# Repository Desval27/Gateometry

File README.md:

# Gateometry

Eight-channel Euclidean rhythm generator for a **classic Arduino Nano, ATmega328P,
16 MHz / 5 V**, using a **128×64 SSD1306 I2C OLED** and Adafruit GFX. This does not
target the Nano Every, Nano ESP32, or a SH1106 display.

## Resources

!Untested!

- [PCB](hardware/README.md)
- [Panel](panel/README.md)

## Build and upload

```sh
pio run
pio run -t upload
```

The existing `nanoatmega328` environment is retained. It uses the old Nano
bootloader setting. For a newer bootloader, change the `board` setting to
`nanoatmega328new`; the environment name can stay unchanged. If necessary set
`upload_port` in `platformio.ini`. PlatformIO installs the Adafruit dependencies.

The sketch starts **stopped**, using the internal clock at **120 BPM**, with
**4 steps per beat** (sixteenth notes). All channels start with **N=16, K=4,
rotation=0, duty=50%**. Settings are RAM-only and return to defaults at power-up.

## Controls and display

- **Run/Stop button:** stop immediately clears all channel gates after button
  debounce. Starting resets every channel and plays slot zero on the next clock
  rising edge. The clock itself keeps running and remains available at Clock Out.
- **Overview:** rotate the encoder to select the header or one of eight channels;
  click to open the selected editor. The header opens global clock settings.
- **Inside either editor:** turn to change the highlighted parameter; click to
  select the next parameter. Hold for 600 ms to return to the overview.
- **Global editor:** choose Internal/External, BPM (20–300), and steps per beat
  (1, 2, 4, or 8). For source selection, clockwise selects External and
  counterclockwise selects Internal. BPM and steps/beat apply to the internal
  clock and the initial external gate-length estimate.
- **Channel editor:** N=1–32, K=0–N, signed rotation=−(N−1)…+(N−1), duty=1–99%.
  Reducing N clamps K and rotation to valid values. Changing a channel parameter
  clears its gate and restarts that channel at slot zero on the next clock;
  the other channels retain their position.
- **Mute toggles:** closed to ground = muted; open = enabled. Muting clears the
  gate after switch debounce; the channel continues counting slots. Unmuting
  waits for the next eligible hit, so it does not create a partial pulse.

Each overview necklace shows every slot, filled hits, and a radial playhead.
Slot zero is at twelve o'clock; time and positive rotation run clockwise.
A diagonal slash marks a muted channel; a small square indicates its gate is
currently high. The selected channel gets a border. The detail page enlarges
its necklace. At 32 slots the small overview is necessarily dense; use the
larger editor to inspect individual slots. The OLED refreshes at about 15 fps,
so very short pulses may not appear in every frame; physical LEDs follow gates.

## Clock and gate behavior

One clock rising edge advances **one slot on every channel**. Each channel wraps
at its own N. For example, N=5 and N=7 realign after 35 clock edges. Euclidean
onsets are evenly distributed with the first unrotated hit at slot zero:
N=8/K=3 gives `10010010`. A positive rotation of one gives `01001001`.

Internal clock interval is `60000 / (BPM × stepsPerBeat)` milliseconds, with a
fractional accumulator to avoid cumulative integer-rounding drift. Clock Out
and the clock LED use approximately 50% duty, and operate even while stopped.
The selected source is explicit; inserting a cable does not automatically
change sources. Changing source clears gates and resets channel positions.

External clock input uses D4's pin-change interrupt. Clock Out and its LED
follow **both edges** of the conditioned input, including while stopped. This
preserves incoming pulse width, with interrupt latency; it is a logic-level
copy, not an analog voltage copy. There is no clock multiplication or division
in external mode: feed a sixteenth-note clock if that is the desired slot rate.

External rising edges closer than 20 ms to the last accepted edge are ignored
by the sequencer (maximum accepted step rate 50 Hz), although Clock Out still
copies them. Use clean, debounced clock edges; this interval guard is not a
replacement for input conditioning. Period measurement supports 20–10,000 ms.
The first pulse, and the first after a gap longer than 10 seconds, uses the
internal BPM/steps setting to estimate its gate length. Following pulses use
the latest measured rising-to-rising interval. The header displays that interval
in milliseconds; `WAIT` appears after the longer of one second or three estimated
periods without a new accepted edge. It does not switch to the internal clock.
If the input stays high, Clock Out stays high as well.

Channel duty is a percentage of **one slot interval**, not the time between
filled slots. Width is quantized to milliseconds, with a minimum of one timer
tick and a maximum one tick shorter than the estimated interval. This leaves a
low gap between adjacent hits. When an external clock suddenly accelerates
before a previous gate has finished, that gate is lowered and retriggered on
the next 1 kHz timer tick. External widths depend on the previous interval,
so abrupt tempo changes cannot have a perfectly predicted duty cycle. If the
external clock disappears, active channel gates still expire normally.

## Nano pin allocation

The pin assignments are fixed in `src/main.cpp`. D2/D3, D4, D5/D6, and D10 use
AVR port/interrupt registers as well as Arduino pin constants; changing those
constants alone is insufficient to move these signals.

| Nano pin | Connection |
| --- | --- |
| D2 / INT0 | Encoder A, contact to ground, internal pull-up |
| D3 / INT1 | Encoder B, contact to ground, internal pull-up |
| D4 / PCINT20 | Conditioned external clock, active high, 0–5 V |
| D5 | Clock Out logic, through output buffer to jack |
| D6 | Clock LED anode through 2.2–4.7 kΩ; cathode to ground |
| D7 | 74HC165 SH/LD (active-low parallel load) |
| D8 | 74HC165 CLK |
| D9 | 74HC165 QH (non-inverted serial output) |
| D10 | 74HC595 RCLK (output latch) |
| D11 / MOSI | 74HC595 SER (serial data) |
| D13 / SCK | 74HC595 SRCLK (shift clock) |
| A0 | Encoder push switch to ground, internal pull-up |
| A1 | 74HC595 OE, with external 10 kΩ pull-up to +5 V |
| A2 | Run/Stop push switch to ground, internal pull-up |
| A4 / SDA | OLED SDA |
| A5 / SCL | OLED SCL |
| D0/D1, D12, A3 | Spare |
| A6/A7 | Unused; analog input only on this Nano |

The encoder common terminal goes to ground. No encoder or button pin is shared
with a jack. Quadrature decoding runs on both encoder interrupts. Set
`EncoderDirection` to −1 if needed; set `EncoderTransitions` to 2 for an encoder
that produces two transitions per detent instead of four.

OLED address defaults to `0x3C`; change `OledAddress` to `0x3D` if necessary.
Use a module compatible with the Nano's 5 V I2C levels, or add appropriate
level translation. A bare SSD1306 panel is not a drop-in 5 V module. The sketch
assumes the module supplies its own reset circuit (no dedicated OLED reset pin).
Use suitable I2C pull-ups and short wiring for the 400 kHz bus.

## Shift registers and output stages

Use **one 74HC595** for the eight gate logic signals, and **one 74HC165** for
the eight mute switches. The 165 uses a separate clock so switch scanning cannot
interfere with interrupt-driven gate updates. Gate LEDs can follow the buffered
gate signals, so no additional LED shift register is necessary.

For the usual 16-pin packages, verify the chosen manufacturer's pinout:

| 74HC595 signal | IC pin | Wire to |
| --- | --- | --- |
| VCC / GND | 16 / 8 | +5 V / ground |
| SER / SRCLK / RCLK | 14 / 11 / 12 | Nano D11 / D13 / D10 |
| OE | 13 | Nano A1 and 10 kΩ pull-up to +5 V |
| SRCLR | 10 | +5 V |
| QA | 15 | Channel 1 buffer input |
| QB…QH | 1…7 | Channels 2…8 buffer inputs |
| QH' | 9 | Unconnected |

Add a 100 kΩ pull-down at each buffer input driven by QA…QH. OE is held high
through reset and bootloader activity; these pull-downs define a low while the
595 outputs are high impedance. The sketch latches zeros before enabling OE.

| 74HC165 signal | IC pin | Wire to |
| --- | --- | --- |
| VCC / GND | 16 / 8 | +5 V / ground |
| SH/LD / CLK / QH | 1 / 2 / 9 | Nano D7 / D8 / D9 |
| CLK INH | 15 | Ground |
| SER | 10 | Ground |
| A / B / C / D | 11 / 12 / 13 / 14 | Channel 1 / 2 / 3 / 4 mute switch |
| E / F / G / H | 3 / 4 / 5 / 6 | Channel 5 / 6 / 7 / 8 mute switch |
| Inverted QH | 7 | Unconnected |

Each A…H input needs its **own 10 kΩ pull-up to +5 V** and a toggle switch to
ground. There are no internal pull-ups in the 165. Place 100 nF decoupling
capacitors at both registers and every buffer IC.

A practical prototype output arrangement is two **74AHCT541 non-inverting
octal buffers**, powered from +5 V. One serves the eight gate outputs; one
channel of the second serves Clock Out. Tie both active-low enables on each
buffer to ground, tie unused inputs to ground, and leave unused outputs open.
Add a 100 kΩ pull-down on the Clock Out buffer input as well.

```text
595 QA..QH ----+--> 74AHCT541 input
              |
             100k
              |
             GND

buffer output ---- 1k ---- gate jack tip
       |
       +---- 4.7k ---- LED anode; LED cathode to GND

Nano D5 --> buffered identically --> clock jack tip
jack sleeves ---------------------> common GND
```

This provides nominal 0/+5 V gates for modules that accept 5 V logic gates.
The series resistor limits short-circuit current and isolates cable loading;
keep per-pin and total package current within the buffer datasheet ratings.
Take the LED branch before the jack's series resistor. The clock LED already
has its own Nano D6 drive. The 595 only drives buffer inputs in this arrangement.
This is a prototype interface suggestion, not a fully protected Eurorack output
circuit: patching an output against an external voltage requires suitable
additional protection, and modules requiring higher gates need another driver.

**Do not connect a raw Eurorack clock jack directly to D4.** A practical
through-hole prototype input stage uses two gates of a **74HCT14 Schmitt-trigger
inverter**, powered from +5 V, and two **Vishay BAT85S Schottky clamp diodes**:

```text
clock jack tip ----+---- 22k ----+---- 74HCT14 ---- 74HCT14 ---- Nano D4
                  |            |      gate 1      gate 2
                 100k          +---- upper clamp to +5 V
                  |            +---- lower clamp to GND
                 GND

jack sleeve ------------------------------------------------ common GND
```

Connect both clamps at the protected node **after the 22 kΩ resistor**, close
to the first gate's input:

| Clamp diode | Anode | Cathode (banded end) |
| --- | --- | --- |
| Upper BAT85S | Protected input node | +5 V |
| Lower BAT85S | GND | Protected input node |

The 100 kΩ jack-to-ground pull-down defines the unplugged state. The 22 kΩ
series resistor limits current when an input goes below ground or above +5 V;
the diodes clamp the protected node near those rails. With approximately 0.3 V
diode drops, a +12 V input produces about 0.30 mA through the upper clamp, and
a −12 V input produces about 0.53 mA through the lower clamp.

The first gate's hysteresis cleans up slow or noisy transitions. The second
gate restores polarity, giving D4 clean, non-inverted 0–5 V logic that idles
low when unplugged. This matters because Clock Out follows both input edges.
The **74HCT14** has lower, TTL-compatible input thresholds than the 74HC14,
giving more margin for 3.3 V clocks while accepting 5 V clocks through the same
network. See the [74HC14/74HCT14 datasheet](https://assets.nexperia.com/documents/data-sheet/74HC_HCT14.pdf).
Place a **100 nF bypass capacitor** directly between the IC's supply pins;
tie unused gate inputs to ground and leave unused outputs unconnected.

The [Vishay BAT85S](https://www.vishay.com/docs/85513/bat85s.pdf) is an axial
**DO-35 through-hole** diode despite its “S” suffix; **BAT85S-TAP** is one
ordering code. It is rated for 30 V reverse voltage and 200 mA forward current,
with a maximum forward drop of 0.32 V at 1 mA at 25°C.

This is a starting circuit for a **powered prototype**, not a fully qualified
Eurorack input. Verify thresholds, clamp voltages and clean edges over the
intended input-voltage and temperature range. The upper clamp injects current
into the +5 V rail: the powered circuit must absorb that current without raising
the rail, and an external clock can partially power the module when it is off.
Powered-off patch protection needs additional circuitry. This analog front end
is separate from the sketch.

Supply the Nano, registers and buffers from a regulated +5 V rail with common
signal ground. A Eurorack +12 V rail must be regulated for these logic parts;
use proper reverse-polarity protection and decoupling at the module power input.
Plan USB/power isolation if the Nano will remain connected to USB while rack
power is present.

## Implementation and validation

- `include/RhythmEngine.h`: portable Euclidean pattern and clock/gate engine.
- `src/main.cpp`: Nano interrupts, shift registers, debounced controls, OLED UI.
- `test/test_engine.cpp`: host-side behavioral regression tests.

Timer1 runs at 1 kHz, owns gate expiration and internal clock generation, and
uses hardware SPI to latch the gate byte. External edges advance directly from
a pin-change ISR. Foreground changes and snapshots use short atomic blocks;
Wire/display operations never occur in interrupts. Timer0 remains available
for Arduino timekeeping. Do not add Servo/Timer1 code or another SPI owner
without redesigning this allocation. The onboard D13 LED will flicker with SPI
traffic; use the separate D6 clock LED on the panel.

An absent OLED leaves clock/gates and physical controls operational with the
default settings. A Wire timeout disables further display refreshes until
reset. Clock/gate interrupts continue during display transfers and timeouts.

Verified with PlatformIO Atmel AVR 5.3.0, Adafruit GFX 1.12.6, and Adafruit
SSD1306 2.5.17: **19,004 bytes flash; 546 bytes static RAM**. SSD1306 allocates
another **1,024 bytes at runtime**, which PlatformIO's RAM summary does not
include. That leaves about **478 bytes before heap bookkeeping and stack**.
Avoid adding `String`, large local arrays, or large libraries without reviewing
memory usage. Stack margin and ISR latency still need measurement on hardware.

Run the portable tests on a host with GCC:

```sh
g++ -std=c++11 -Wall -Wextra -Werror -pedantic \
    -fsanitize=address,undefined -Iinclude test/test_engine.cpp \
    -o /tmp/gateometry-test
/tmp/gateometry-test
```

The tests check every supported N/K/rotation combination, equal-spacing gaps,
clock counts at several BPM/subdivision extremes, gate-width bounds, run/stop,
independent channel lengths/duties, mute/unmute, external period estimation,
sudden tempo changes/retriggering, slow clocks, clock loss, and timer rollover.
The firmware builds and these tests pass. **Physical hardware has not been
exercised**. Before connecting other modules, verify output polarity/levels,
channel ordering, boot-time silence, encoder detents, input conditioning, and
clock/gate timing on a scope, including during OLED updates.

## References

- [Arduino Nano specifications](https://store.arduino.cc/arduino-nano)
- [ATmega328P datasheet: interrupt and timer registers](https://docs.arduino.cc/resources/datasheets/ATmega328P-datasheet.pdf)
- [PlatformIO Nano configuration](https://docs.platformio.org/en/latest/boards/atmelavr/nanoatmega328.html)
- [Adafruit SSD1306 implementation and framebuffer allocation](https://github.com/adafruit/Adafruit_SSD1306/blob/master/Adafruit_SSD1306.cpp)
- [TI 74HC595 datasheet](https://www.ti.com/lit/ds/symlink/sn74hc595.pdf)
- [TI 74HC165 datasheet and pinout](https://www.ti.com/product/SN74HC165)
- [TI 74AHCT541 buffer specifications](https://www.ti.com/product/SN74AHCT541)

## ⚠️ Disclaimer⚠️

This project is provided **"as is"**, without warranty of any kind, express or implied,
including but not limited to the warranties of merchantability, fitness for a
particular purpose, and noninfringement.

This is a DIY electronics project intended for educational and experimental use.
Use at your own risk.

The author assumes **no responsibility or liability** for any damage, injury, or loss
resulting from the use or misuse of this design, including but not limited to:

* Damage to connected equipment (Eurorack modules, power supplies, computers, etc.)
* Incorrect assembly or wiring
* Use with incompatible voltages or signal levels
* Personal injury

### Electrical Safety

This project may interface with:

* ±12V & +5V Power rails
* AC Mains Power (Lethal Risk)
* External control voltages (CV)
* Digital and analog circuitry

Improper handling may result in damage or unsafe conditions.

You are responsible for:

* Verifying all connections before powering the system
* Ensuring correct polarity of power connections
* Confirming voltage ranges and signal compatibility
* Using appropriate protection circuits where necessary

### No Guarantees

Schematics, PCB layouts, and code are provided for reference only.
They may contain errors, omissions, or design flaws.

**Always review and validate the design before building or using it.**

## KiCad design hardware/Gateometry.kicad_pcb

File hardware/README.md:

# GATEOMETRY PCB

!Untested!

**Gateometry** is an eight-channel **Euclidean** rhythm generator for **Eurorack** modular synthesizers, built around an **Arduino Nano**. It generates programmable rhythmic gate patterns using the Euclidean algorithm, with independently configurable steps, pulses, rotation, and muting for each channel. The PCB integrates external clock and reset inputs, clock output, eight gate outputs, a rotary encoder for menu navigation, an OLED display, and dedicated run/stop and mute controls. Designed as a flexible platform for rhythmic experimentation, **Gateometry** combines algorithmic pattern generation with hands-on control and external clock synchronization.

## RESOURCES

- [Schematic](schematic.pdf)
- [Assembly](assembly.pdf)
- [Bill of Materials](bom.csv)
- [Interactive Bill of Materials](ibom.html)

## GERBER TO ORDER

- [Default](gerber_to_order/Gateometry_191.3x150.0mm_for_Default.zip)
- [Elecrow](gerber_to_order/Gateometry_191.3x150.0mm_for_Elecrow.zip)
- [FusionPCB](gerber_to_order/Gateometry_191.3x150.0mm_for_FusionPCB.zip)
- [JLCPCB](gerber_to_order/Gateometry_191.3x150.0mm_for_JLCPCB.zip)
- [PCBWay](gerber_to_order/Gateometry_191.3x150.0mm_for_PCBWay.zip)

## RENDERS

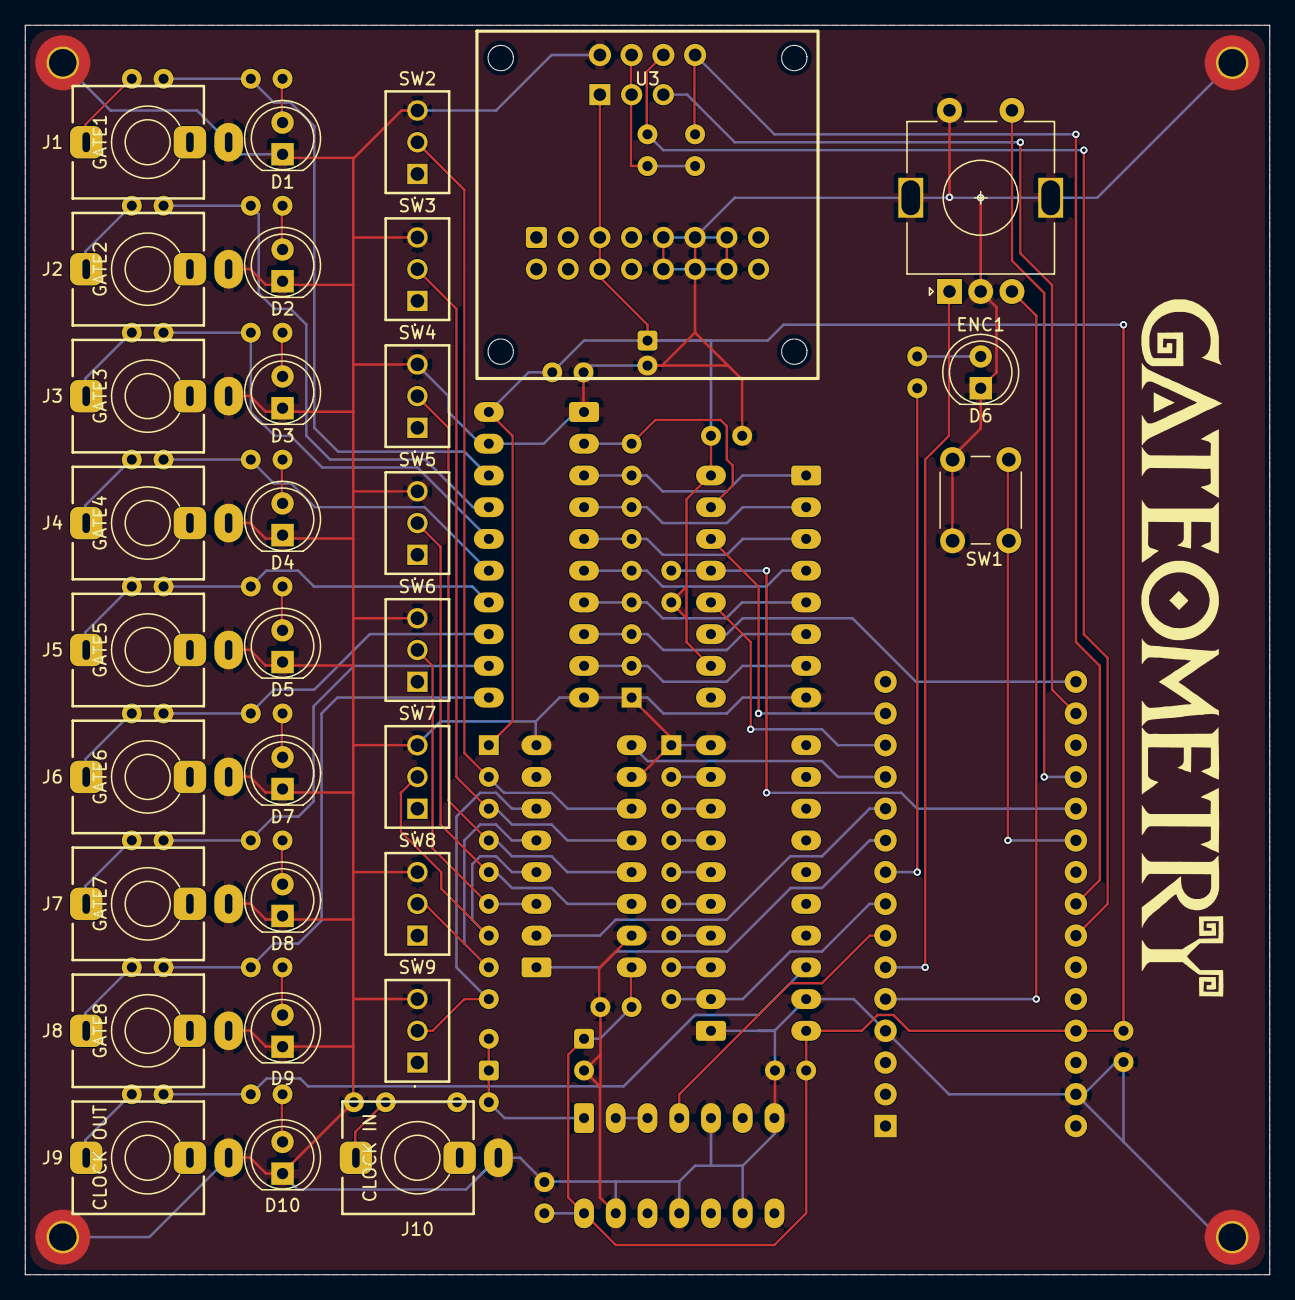
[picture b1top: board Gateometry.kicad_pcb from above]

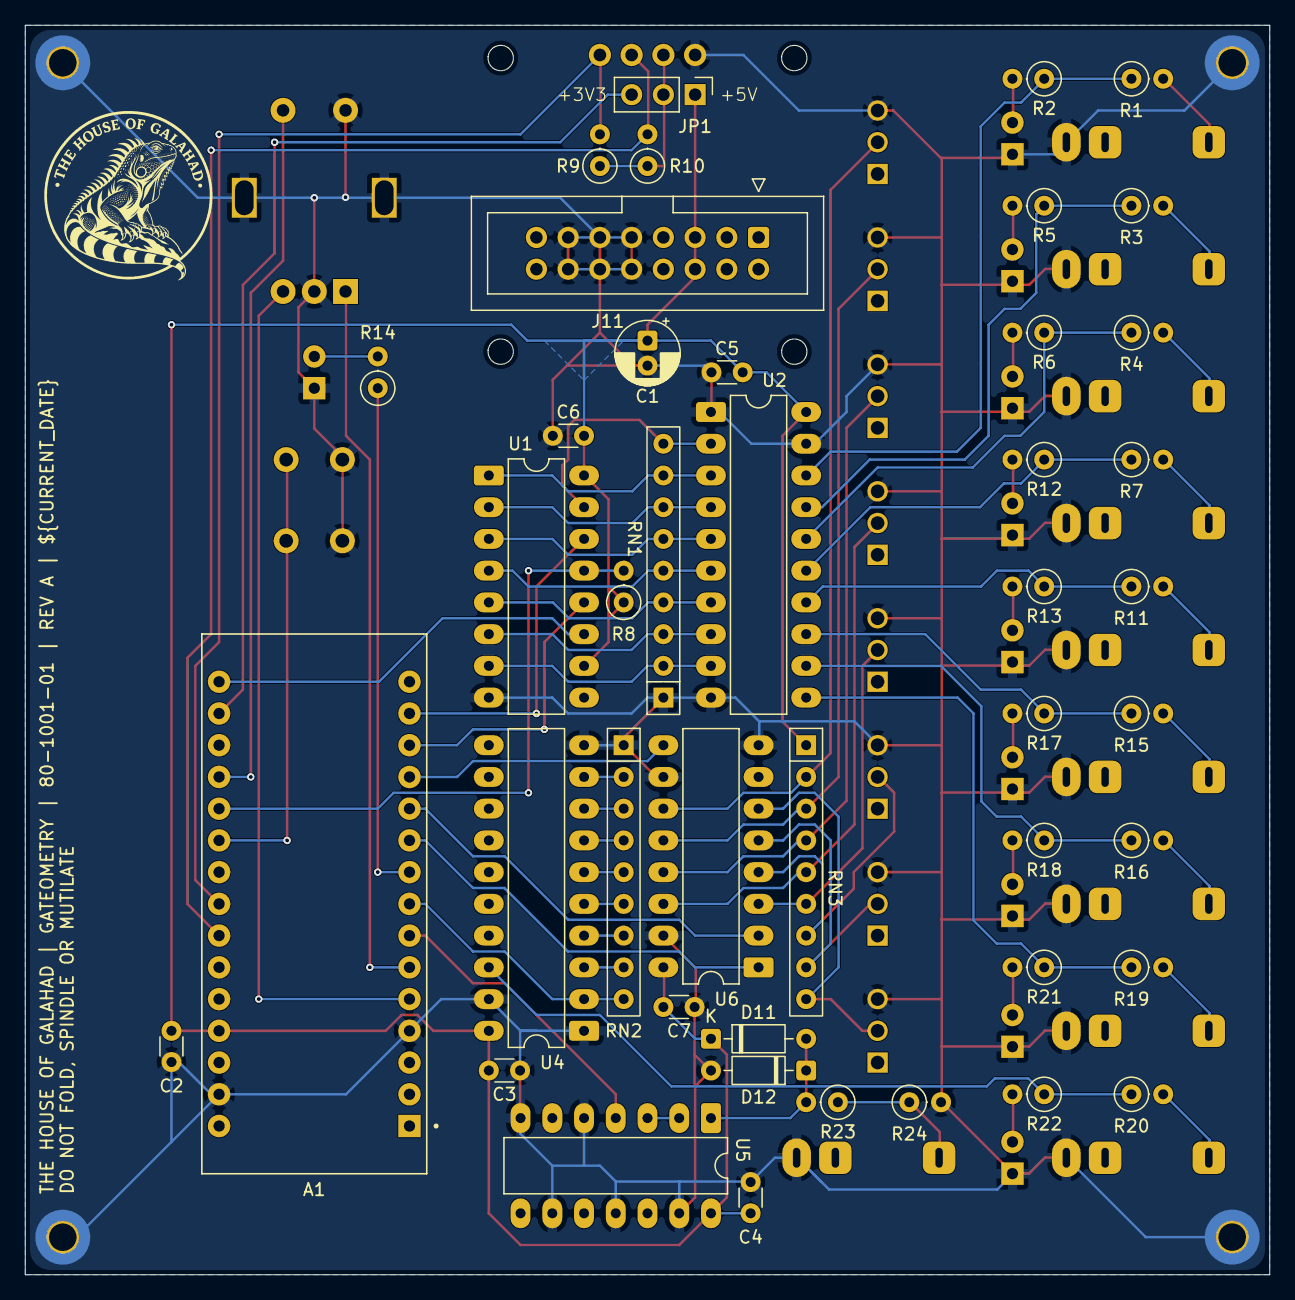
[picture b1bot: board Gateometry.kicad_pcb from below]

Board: 2 copper layers, 99.6 x 100.0 mm, 79 parts (44 on the bottom side), 74 nets.

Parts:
A1: Arduino_Nano_v3.x; MODULE_ARDUINO_NANO
C1: 47µ; CP_Radial_D5.0mm_P2.00mm
C2, C3, C4, C5, C6, C7: 100n; C_Disc_D3.0mm_W1.6mm_P2.50mm
D1: GATE1 LED; LED_D5.0mm_FlatTop
D2: GATE2 LED; LED_D5.0mm_FlatTop
D3: GATE3 LED; LED_D5.0mm_FlatTop
D4: GATE4 LED; LED_D5.0mm_FlatTop
D5: GATE5 LED; LED_D5.0mm_FlatTop
D6: CLOCK LED; LED_D5.0mm_FlatTop
D7: GATE6 LED; LED_D5.0mm_FlatTop
D8: GATE7 LED; LED_D5.0mm_FlatTop
D9: GATE8 LED; LED_D5.0mm_FlatTop
D10: CLOCK OUT LED; LED_D5.0mm_FlatTop
D11, D12: BAT85; D_DO-35_SOD27_P7.62mm_Horizontal
ENC1: ROTARY ENCODER; Rotary Encoder
H1, H2, H3, H4: MountingHole_Pad; MountingHole_2.2mm_M2_Pad_TopBottom
J1: GATE1; Jack_3.5mm_QingPu_WQP-PJ398SM_Vertical
J2: GATE2; Jack_3.5mm_QingPu_WQP-PJ398SM_Vertical
J3: GATE3; Jack_3.5mm_QingPu_WQP-PJ398SM_Vertical
J4: GATE4; Jack_3.5mm_QingPu_WQP-PJ398SM_Vertical
J5: GATE5; Jack_3.5mm_QingPu_WQP-PJ398SM_Vertical
J6: GATE6; Jack_3.5mm_QingPu_WQP-PJ398SM_Vertical
J7: GATE7; Jack_3.5mm_QingPu_WQP-PJ398SM_Vertical
J8: GATE8; Jack_3.5mm_QingPu_WQP-PJ398SM_Vertical
J9: CLOCK OUT; Jack_3.5mm_QingPu_WQP-PJ398SM_Vertical
J10: CLOCK IN; Jack_3.5mm_QingPu_WQP-PJ398SM_Vertical
J11: POWER; IDC-Header_2x08_P2.54mm_Vertical
JP1: OLED POWER; PinHeader_1x03_P2.54mm_Vertical
R1, R3, R4, R7, R11, R15, R16, R19, R20: 1k; R_Axial_DIN0207_L6.3mm_D2.5mm_P2.54mm_Vertical
R2, R5, R6, R12, R13, R17, R18, R21, R22: 4k7; R_Axial_DIN0207_L6.3mm_D2.5mm_P2.54mm_Vertical
R8, R9, R10: 10k; R_Axial_DIN0207_L6.3mm_D2.5mm_P2.54mm_Vertical
R14: 2k2; R_Axial_DIN0207_L6.3mm_D2.5mm_P2.54mm_Vertical
R23: 22k; R_Axial_DIN0207_L6.3mm_D2.5mm_P2.54mm_Vertical
R24: 100k; R_Axial_DIN0207_L6.3mm_D2.5mm_P2.54mm_Vertical
RN1, RN2: 100k; R_Array_SIP9
RN3: 10k; R_Array_SIP9
SW1: RUN/STOP; SW_PUSH_6mm_H8mm
SW2: MUTE1; 2MS1T1B1M2QES
SW3: MUTE2; 2MS1T1B1M2QES
SW4: MUTE3; 2MS1T1B1M2QES
SW5: MUTE4; 2MS1T1B1M2QES
SW6: MUTE5; 2MS1T1B1M2QES
SW7: MUTE6; 2MS1T1B1M2QES
SW8: MUTE7; 2MS1T1B1M2QES
SW9: MUTE8; 2MS1T1B1M2QES
U1: 74HC595; DIP-16_W7.62mm_LongPads
U2, U4: 74HCT541; DIP-20_W7.62mm_LongPads
U3: 0.96 Inch OLED I2C Display Module
U5: 74HCT14; DIP-14_W7.62mm_LongPads
U6: 74HC165; DIP-16_W7.62mm_LongPads

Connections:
+3V3: A1.17 (3V3), JP1.3 (B)
+5V: A1.27 (+5V), C1.1, C2.1, C3.1, C4.1, C5.1, C6.1, C7.1, D11.1 (K), J11.5 (+12V), J11.6, JP1.1 (A), R8.1, RN3.1 (common), U1.10 (~SRCLR), U1.16 (VCC), U2.20 (VCC), U4.20 (VCC), U5.14 (VCC), U6.16 (VCC)
CLOCK IN: A1.7 (D4), U5.4
CLOCK OUT: A1.8 (D5), RN2.9 (R8), U4.2 (A0)
GND: A1.4 (GND), A1.29 (GND), C1.2, C2.2, C3.2, C4.2, C5.2, C6.2, C7.2, D1.1 (K), D2.1 (K), D3.1 (K), D4.1 (K), D5.1 (K), D6.1 (K), D7.1 (K), D8.1 (K), D9.1 (K), D10.1 (K), D12.2 (A), ENC1.C, ENC1.MP, ENC1.S2, H1.1 (1_1), H2.1 (1_1), H3.1 (1_1), H4.1 (1_1), J1.S (SHEILD), J2.S (SHEILD), J3.S (SHEILD), J4.S (SHEILD), J5.S (SHEILD), J6.S (SHEILD), J7.S (SHEILD), J8.S (SHEILD), J9.S (SHEILD), J10.S (SHEILD), J11.9 (GND), J11.10 (GND), J11.11 (GND), J11.12 (GND), J11.13 (-12), J11.14 (-12V), R24.2, RN1.1 (common), RN2.1 (common), SW1.2 (B), SW2.3 (C), SW3.3 (C), SW4.3 (C), SW5.3 (C), SW6.3 (C), SW7.3 (C), SW8.3 (C), SW9.3 (C), U1.8 (GND), U2.1 (G1), U2.10 (GND), U2.19 (G2), U3.1 (GND), U4.1 (G1), U4.10 (GND), U4.19 (G2), U5.5, U5.7 (GND), U5.9, U5.11, U5.13, U6.8 (GND), U6.10 (DS), U6.15 (~CE)
unnamed: A1.19 (A0), ENC1.S1
unnamed: A1.20 (A1), R8.2, U1.13 (~OE)
unnamed: A1.21 (A2), SW1.1 (A)
unnamed: A1.23 (A4), R9.2, U3.4 (SDA)
unnamed: A1.24 (A5), R10.2, U3.3 (SCL)
unnamed: A1.5 (D2), ENC1.B
unnamed: A1.6 (D3), ENC1.A
unnamed: A1.9 (D6), R14.1
unnamed: A1.10 (D7), U6.1 (~PL)
unnamed: A1.11 (D8), U6.2 (CP)
unnamed: A1.12 (D9), U6.9 (Q7)
unnamed: A1.13 (D10), U1.12 (RCLK)
unnamed: A1.14 (D11), U1.14 (SER)
unnamed: A1.16 (D13), U1.11 (SRCLK)
unnamed: D1.2 (A), R2.2
unnamed: D2.2 (A), R5.2
unnamed: D3.2 (A), R6.2
unnamed: D4.2 (A), R12.2
unnamed: D5.2 (A), R13.2
unnamed: D6.2 (A), R14.2
unnamed: D7.2 (A), R17.2
unnamed: D8.2 (A), R18.2
unnamed: D9.2 (A), R21.2
unnamed: D10.2 (A), R22.2
unnamed: D11.2 (A), D12.1 (K), R23.2, U5.1
unnamed: J1.T (SIG), R1.2
unnamed: J2.T (SIG), R3.2
unnamed: J3.T (SIG), R4.2
unnamed: J4.T (SIG), R7.2
unnamed: J5.T (SIG), R11.2
unnamed: J6.T (SIG), R15.2
unnamed: J7.T (SIG), R16.2
unnamed: J8.T (SIG), R19.2
unnamed: J9.T (SIG), R20.2
unnamed: J10.T (SIG), R23.1, R24.1
unnamed: JP1.2 (C), R9.1, R10.1, U3.2 (VCC)
unnamed: RN1.2 (R1), U1.7 (QH), U2.9 (A7)
unnamed: RN1.3 (R2), U1.6 (QG), U2.8 (A6)
unnamed: RN1.4 (R3), U1.5 (QF), U2.7 (A5)
unnamed: RN1.5 (R4), U1.4 (QE), U2.6 (A4)
unnamed: RN1.6 (R5), U1.3 (QD), U2.5 (A3)
unnamed: RN1.7 (R6), U1.2 (QC), U2.4 (A2)
unnamed: RN1.8 (R7), U1.1 (QB), U2.3 (A1)
unnamed: RN1.9 (R8), U1.15 (QA), U2.2 (A0)
unnamed: RN2.2 (R1), U4.9 (A7)
unnamed: RN2.3 (R2), U4.8 (A6)
unnamed: RN2.4 (R3), U4.7 (A5)
unnamed: RN2.5 (R4), U4.6 (A4)
unnamed: RN2.6 (R5), U4.5 (A3)
unnamed: RN2.7 (R6), U4.4 (A2)
unnamed: RN2.8 (R7), U4.3 (A1)
unnamed: RN3.2 (R1), SW2.2 (B), U6.11 (D0)
unnamed: RN3.3 (R2), SW3.2 (B), U6.12 (D1)
unnamed: RN3.4 (R3), SW4.2 (B), U6.13 (D2)
unnamed: RN3.5 (R4), SW5.2 (B), U6.14 (D3)
unnamed: RN3.6 (R5), SW6.2 (B), U6.3 (D4)
unnamed: RN3.7 (R6), SW7.2 (B), U6.4 (D5)
unnamed: RN3.8 (R7), SW8.2 (B), U6.5 (D6)
unnamed: RN3.9 (R8), SW9.2 (B), U6.6 (D7)
unnamed: R1.1, R2.1, U2.18 (Y0)
unnamed: R3.1, R5.1, U2.17 (Y1)
unnamed: R4.1, R6.1, U2.16 (Y2)
unnamed: R7.1, R12.1, U2.15 (Y3)
unnamed: R11.1, R13.1, U2.14 (Y4)
unnamed: R15.1, R17.1, U2.13 (Y5)
unnamed: R16.1, R18.1, U2.12 (Y6)
unnamed: R19.1, R21.1, U2.11 (Y7)
unnamed: R20.1, R22.1, U4.18 (Y0)
unnamed: U5.2, U5.3

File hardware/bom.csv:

"Reference","Qty","Value","DNP","Exclude from BOM","Exclude from Board","Exclude from Simulation","Exclude from Position Files","Footprint","Datasheet"
"A1","1","Arduino_Nano_v3.x","","","","","${EXCLUDE_FROM_POS_FILES}","Desval27:MODULE_ARDUINO_NANO","http://www.mouser.com/pdfdocs/Gravitech_Arduino_Nano3_0.pdf"
"C1","1","47µ","","","","","${EXCLUDE_FROM_POS_FILES}","Capacitor_THT:CP_Radial_D5.0mm_P2.00mm",""
"C2,C3,C4,C5,C6,C7","6","100n","","","","","${EXCLUDE_FROM_POS_FILES}","Capacitor_THT:C_Disc_D3.0mm_W1.6mm_P2.50mm",""
"D1","1","GATE1 LED","","","","","${EXCLUDE_FROM_POS_FILES}","LED_THT:LED_D5.0mm_FlatTop",""
"D2","1","GATE2 LED","","","","","${EXCLUDE_FROM_POS_FILES}","LED_THT:LED_D5.0mm_FlatTop",""
"D3","1","GATE3 LED","","","","","${EXCLUDE_FROM_POS_FILES}","LED_THT:LED_D5.0mm_FlatTop",""
"D4","1","GATE4 LED","","","","","${EXCLUDE_FROM_POS_FILES}","LED_THT:LED_D5.0mm_FlatTop",""
"D5","1","GATE5 LED","","","","","${EXCLUDE_FROM_POS_FILES}","LED_THT:LED_D5.0mm_FlatTop",""
"D6","1","CLOCK LED","","","","","${EXCLUDE_FROM_POS_FILES}","LED_THT:LED_D5.0mm_FlatTop",""
"D7","1","GATE6 LED","","","","","${EXCLUDE_FROM_POS_FILES}","LED_THT:LED_D5.0mm_FlatTop",""
"D8","1","GATE7 LED","","","","","${EXCLUDE_FROM_POS_FILES}","LED_THT:LED_D5.0mm_FlatTop",""
"D9","1","GATE8 LED","","","","","${EXCLUDE_FROM_POS_FILES}","LED_THT:LED_D5.0mm_FlatTop",""
"D10","1","CLOCK OUT LED","","","","","${EXCLUDE_FROM_POS_FILES}","LED_THT:LED_D5.0mm_FlatTop",""
"D11,D12","2","BAT85","","","","","${EXCLUDE_FROM_POS_FILES}","Diode_THT:D_DO-35_SOD27_P7.62mm_Horizontal","https://assets.nexperia.com/documents/data-sheet/BAT85.pdf"
"ENC1","1","ROTARY ENCODER","","","","","${EXCLUDE_FROM_POS_FILES}","Desval27:Rotary Encoder",""
"J1","1","GATE1","","","","","${EXCLUDE_FROM_POS_FILES}","Desval27:Jack_3.5mm_QingPu_WQP-PJ398SM_Vertical",""
"J2","1","GATE2","","","","","${EXCLUDE_FROM_POS_FILES}","Desval27:Jack_3.5mm_QingPu_WQP-PJ398SM_Vertical",""
"J3","1","GATE3","","","","","${EXCLUDE_FROM_POS_FILES}","Desval27:Jack_3.5mm_QingPu_WQP-PJ398SM_Vertical",""
"J4","1","GATE4","","","","","${EXCLUDE_FROM_POS_FILES}","Desval27:Jack_3.5mm_QingPu_WQP-PJ398SM_Vertical",""
"J5","1","GATE5","","","","","${EXCLUDE_FROM_POS_FILES}","Desval27:Jack_3.5mm_QingPu_WQP-PJ398SM_Vertical",""
"J6","1","GATE6","","","","","${EXCLUDE_FROM_POS_FILES}","Desval27:Jack_3.5mm_QingPu_WQP-PJ398SM_Vertical",""
"J7","1","GATE7","","","","","${EXCLUDE_FROM_POS_FILES}","Desval27:Jack_3.5mm_QingPu_WQP-PJ398SM_Vertical",""
"J8","1","GATE8","","","","","${EXCLUDE_FROM_POS_FILES}","Desval27:Jack_3.5mm_QingPu_WQP-PJ398SM_Vertical",""
"J9","1","CLOCK OUT","","","","","${EXCLUDE_FROM_POS_FILES}","Desval27:Jack_3.5mm_QingPu_WQP-PJ398SM_Vertical",""
"J10","1","CLOCK IN","","","","","${EXCLUDE_FROM_POS_FILES}","Desval27:Jack_3.5mm_QingPu_WQP-PJ398SM_Vertical",""
"J11","1","POWER","","","","","${EXCLUDE_FROM_POS_FILES}","Connector_IDC:IDC-Header_2x08_P2.54mm_Vertical",""
"R1,R3,R4,R7,R11,R15,R16,R19,R20","9","1k","","","","","${EXCLUDE_FROM_POS_FILES}","Resistor_THT:R_Axial_DIN0207_L6.3mm_D2.5mm_P2.54mm_Vertical",""
"R2,R5,R6,R12,R13,R17,R18,R21,R22","9","4k7","","","","","${EXCLUDE_FROM_POS_FILES}","Resistor_THT:R_Axial_DIN0207_L6.3mm_D2.5mm_P2.54mm_Vertical",""
"R8,R9,R10","3","10k","","","","","${EXCLUDE_FROM_POS_FILES}","Resistor_THT:R_Axial_DIN0207_L6.3mm_D2.5mm_P2.54mm_Vertical",""
"R14","1","2k2","","","","","${EXCLUDE_FROM_POS_FILES}","Resistor_THT:R_Axial_DIN0207_L6.3mm_D2.5mm_P2.54mm_Vertical",""
"R23","1","22k","","","","","${EXCLUDE_FROM_POS_FILES}","Resistor_THT:R_Axial_DIN0207_L6.3mm_D2.5mm_P2.54mm_Vertical",""
"R24","1","100k","","","","","${EXCLUDE_FROM_POS_FILES}","Resistor_THT:R_Axial_DIN0207_L6.3mm_D2.5mm_P2.54mm_Vertical",""
"RN1,RN2","2","100k","","","","","${EXCLUDE_FROM_POS_FILES}","Resistor_THT:R_Array_SIP9","http://www.vishay.com/docs/31509/csc.pdf"
"RN3","1","10k","","","","","${EXCLUDE_FROM_POS_FILES}","Resistor_THT:R_Array_SIP9","http://www.vishay.com/docs/31509/csc.pdf"
"SW1","1","RUN/STOP","","","","","${EXCLUDE_FROM_POS_FILES}","Button_Switch_THT:SW_PUSH_6mm_H8mm",""
"SW2","1","MUTE 1","","","","","${EXCLUDE_FROM_POS_FILES}","Desval27:2MS1T1B1M2QES",""
"SW3","1","MUTE 2","","","","","${EXCLUDE_FROM_POS_FILES}","Desval27:2MS1T1B1M2QES",""
"SW4","1","MUTE 3","","","","","${EXCLUDE_FROM_POS_FILES}","Desval27:2MS1T1B1M2QES",""
"SW5","1","MUTE 4","","","","","${EXCLUDE_FROM_POS_FILES}","Desval27:2MS1T1B1M2QES",""
"SW6","1","MUTE 5","","","","","${EXCLUDE_FROM_POS_FILES}","Desval27:2MS1T1B1M2QES",""
"SW7","1","MUTE 6","","","","","${EXCLUDE_FROM_POS_FILES}","Desval27:2MS1T1B1M2QES",""
"SW8","1","MUTE 7","","","","","${EXCLUDE_FROM_POS_FILES}","Desval27:2MS1T1B1M2QES",""
"SW9","1","MUTE 8","","","","","${EXCLUDE_FROM_POS_FILES}","Desval27:2MS1T1B1M2QES",""
"U1","1","74HC595","","","","","${EXCLUDE_FROM_POS_FILES}","Package_DIP:DIP-16_W7.62mm_LongPads","http://www.ti.com/lit/ds/symlink/sn74hc595.pdf"
"U2,U4","2","74HCT541","","","","","${EXCLUDE_FROM_POS_FILES}","Package_DIP:DIP-20_W7.62mm_LongPads","http://www.ti.com/lit/gpn/sn74HCT541"
"U3","1","0.96 Inch OLED I2C Display Module","","","","","${EXCLUDE_FROM_POS_FILES}","Desval27:0.96 Inch OLED I2C Display Module","https://atta.szlcsc.com/upload/public/pdf/source/20240311/1D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"
"U5","1","74HCT14","","","","","${EXCLUDE_FROM_POS_FILES}","Package_DIP:DIP-14_W7.62mm_LongPads","http://www.ti.com/lit/gpn/sn74HC14"
"U6","1","74HC165","","","","","${EXCLUDE_FROM_POS_FILES}","Package_DIP:DIP-16_W7.62mm_LongPads","https://assets.nexperia.com/documents/data-sheet/74HC_HCT165.pdf"

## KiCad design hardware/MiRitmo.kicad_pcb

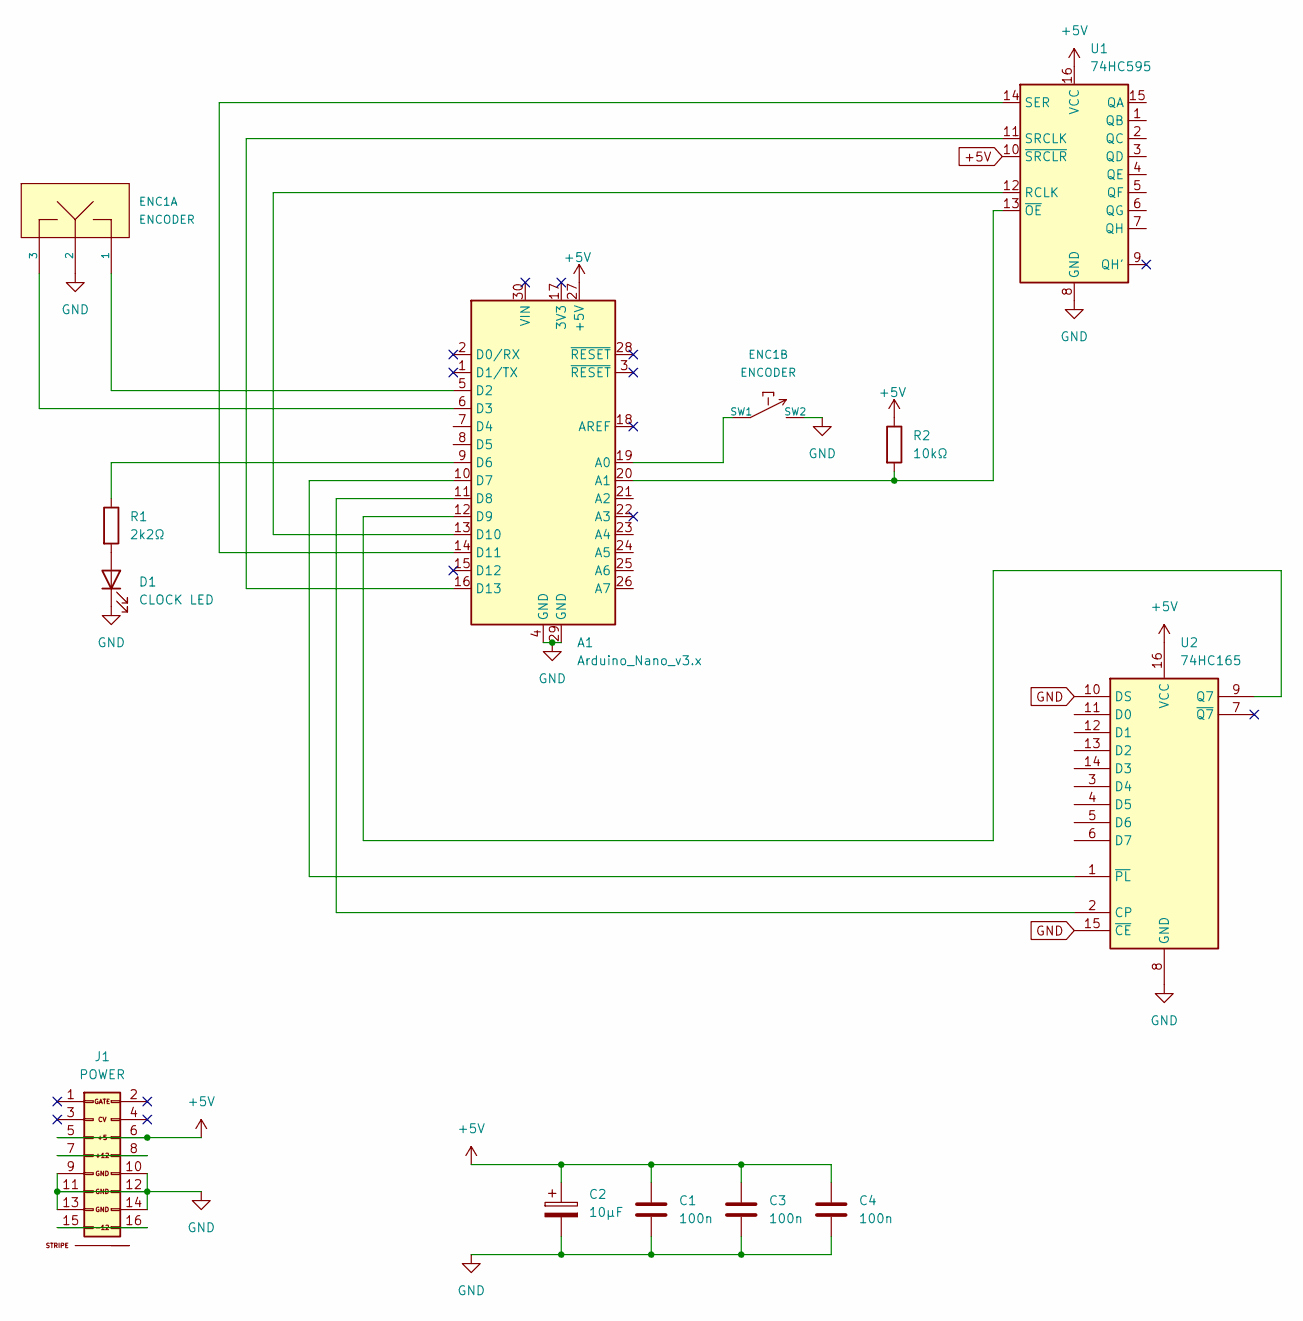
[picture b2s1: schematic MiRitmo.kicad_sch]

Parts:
A1: Arduino_Nano_v3.x; Arduino_Nano
C1, C3, C4: 100n; C_Disc_D3.0mm_W1.6mm_P2.50mm
C2: 10µF; CP_Radial_D5.0mm_P2.00mm
D1: CLOCK LED; LED_D5.0mm_FlatTop
ENC1: ENCODER; ENC_SPST_12mm; Part Number RE111F-41B3N-20F-20P-N
J1: POWER; Pins_2x08_2.54mm_TH_EuroPower_Shrouded; Part Number LL1007-1 (2*8 HITEMP)
R1: 2k2Ω; R_Axial_DIN0207_L6.3mm_D2.5mm_P10.16mm_Horizontal
R2: 10kΩ; R_Axial_DIN0207_L6.3mm_D2.5mm_P10.16mm_Horizontal
U1: 74HC595; DIP-16_W7.62mm_LongPads
U2: 74HC165; DIP-16_W7.62mm_LongPads

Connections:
+5V: A1.27 (+5V), C1.1, C2.1, C3.1, C4.1, J1.5 (+12V), J1.6, R2.1, U1.10 (~SRCLR), U1.16 (VCC), U2.16 (VCC)
GND: A1.4 (GND), A1.29 (GND), C1.2, C2.2, C3.2, C4.2, D1.1 (K), ENC1.2, ENC1.SW2, J1.9 (GND), J1.10 (GND), J1.11 (GND), J1.12 (GND), J1.13 (-12), J1.14 (-12V), U1.8 (GND), U2.8 (GND), U2.10 (DS), U2.15 (~CE)
unnamed: A1.19 (A0), ENC1.SW1
unnamed: A1.20 (A1), R2.2, U1.13 (~OE)
unnamed: A1.5 (D2), ENC1.1
unnamed: A1.6 (D3), ENC1.3
unnamed: A1.9 (D6), R1.1
unnamed: A1.10 (D7), U2.1 (~PL)
unnamed: A1.11 (D8), U2.2 (CP)
unnamed: A1.12 (D9), U2.9 (Q7)
unnamed: A1.13 (D10), U1.12 (RCLK)
unnamed: A1.14 (D11), U1.14 (SER)
unnamed: A1.16 (D13), U1.11 (SRCLK)
unnamed: D1.2 (A), R1.2
unnamed: J1.7 (12V), J1.8 (+12V)
unnamed: J1.15 (-12V), J1.16

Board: 2 copper layers, 12 parts (10 on the bottom side), 16 nets, no tracks yet.
